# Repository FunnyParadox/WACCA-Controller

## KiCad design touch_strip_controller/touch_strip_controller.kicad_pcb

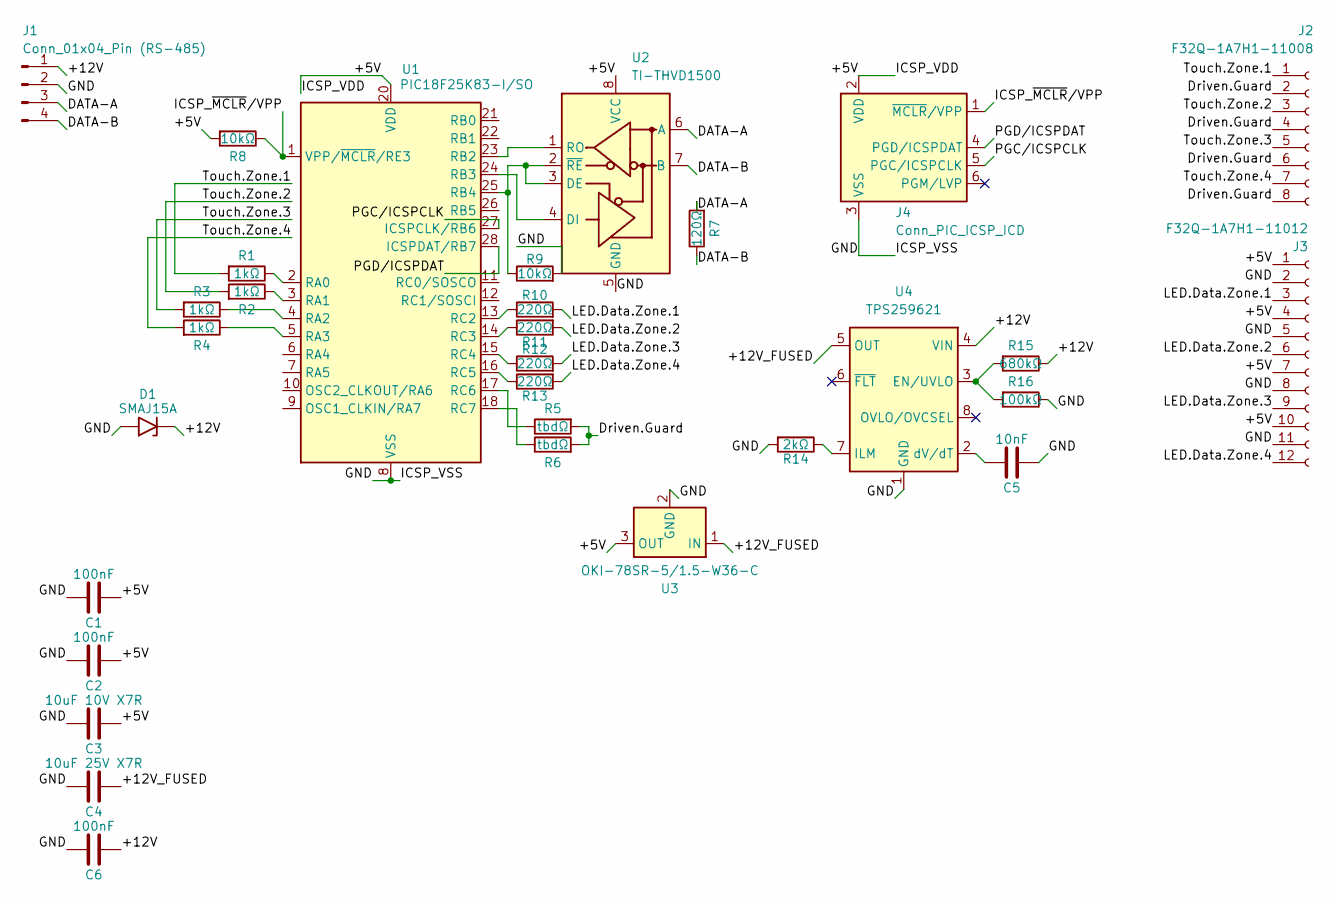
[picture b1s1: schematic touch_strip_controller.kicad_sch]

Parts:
C1, C2, C6: 100nF; C_0603_1608Metric
C3: 10uF 10V X7R; C_1206_3216Metric
C4: 10uF 25V X7R; C_1206_3216Metric
C5: 10nF; C_0603_1608Metric
D1: SMAJ15A; D_SMA
J1: Conn_01x04_Pin (RS-485); Amphenol_F32Q-1A7x1-11004_1x04-1MP_P0.5mm_Horizontal
J2: F32Q-1A7H1-11008; Amphenol_F32Q-1A7x1-11008_1x08-1MP_P0.5mm_Horizontal
J3: F32Q-1A7H1-11012; Amphenol_F32Q-1A7x1-11012_1x12-1MP_P0.5mm_Horizontal
J4: Conn_PIC_ICSP_ICD; PinHeader_1x06_P2.54mm_Vertical
R1, R2, R3, R4: 1kΩ; R_0603_1608Metric
R5, R6: tbdΩ; R_0603_1608Metric
R7: 120Ω; R_0603_1608Metric
R8, R9: 10kΩ; R_0603_1608Metric
R10, R11, R12, R13: 220Ω; R_0603_1608Metric
R14: 2kΩ; R_0603_1608Metric
R15: 680kΩ; R_0603_1608Metric
R16: 100kΩ; R_0603_1608Metric
U1: PIC18F25K83-I/SO; SOIC-28W_7.5x17.9mm_P1.27mm
U2: TI-THVD1500; SOIC-8_3.9x4.9mm_P1.27mm
U3: OKI-78SR-5/1.5-W36-C; Converter_DCDC_Murata_OKI-78SR_Vertical
U4: TPS259621; TI_SO-PowerPAD-8_ThermalVias

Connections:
/+5V: C1.1, C2.1, C3.1, J3.1, J3.4, J3.7, J3.10, J4.2 (VDD), R8.2, U1.20 (VDD), U2.8 (VCC), U3.3 (OUT)
/+12V: C6.2, D1.1 (A1), J1.1, R15.1, U4.4 (VIN)
/+12V_FUSED: C4.1, U3.1 (IN), U4.5 (OUT)
/DATA-A: J1.3, R7.2, U2.6 (A)
/DATA-B: J1.4, R7.1, U2.7 (B)
/Driven.Guard: J2.2, J2.4, J2.6, J2.8, R5.2, R6.2
/GND: C1.2, C2.2, C3.2, C4.2, C5.2, C6.1, D1.2 (A2), J1.2, J3.2, J3.5, J3.8, J3.11, J4.3 (VSS), R9.2, R14.2, R16.1, U1.8 (VSS), U1.19 (VSS), U2.5 (GND), U3.2 (GND), U4.1 (GND), U4.9 (GND)
/ICSP_~MCLR/VPP: J4.1 (~MCLR/VPP), R8.1, U1.1 (VPP/~MCLR/RE3)
/LED.Data.Zone.1: J3.3, R10.2
/LED.Data.Zone.2: J3.6, R11.2
/LED.Data.Zone.3: J3.9, R12.2
/LED.Data.Zone.4: J3.12, R13.2
/PGC/ICSPCLK: J4.5 (PGC/ICSPCLK), U1.27 (ICSPCLK/RB6)
/PGD/ICSPDAT: J4.4 (PGD/ICSPDAT), U1.28 (ICSPDAT/RB7)
/Touch.Zone.1: J2.1, R1.2
/Touch.Zone.2: J2.3, R2.2
/Touch.Zone.3: J2.5, R3.2
/Touch.Zone.4: J2.7, R4.2
unnamed: R1.1, U1.2 (RA0)
unnamed: R2.1, U1.3 (RA1)
unnamed: R3.1, U1.4 (RA2)
unnamed: R4.1, U1.5 (RA3)
unnamed: U1.23 (RB2), U2.1 (RO)
unnamed: U1.24 (RB3), U2.4 (DI)
unnamed: R9.1, U1.25 (RB4), U2.2 (~RE), U2.3 (DE)
unnamed: R10.1, U1.13 (RC2)
unnamed: R11.1, U1.14 (RC3)
unnamed: R12.1, U1.15 (RC4)
unnamed: R13.1, U1.16 (RC5)
unnamed: R5.1, U1.17 (RC6)
unnamed: R6.1, U1.18 (RC7)
unnamed: R15.2, R16.2, U4.3 (EN/UVLO)
unnamed: R14.1, U4.7 (ILM)
unnamed: C5.1, U4.2 (dV/dT)

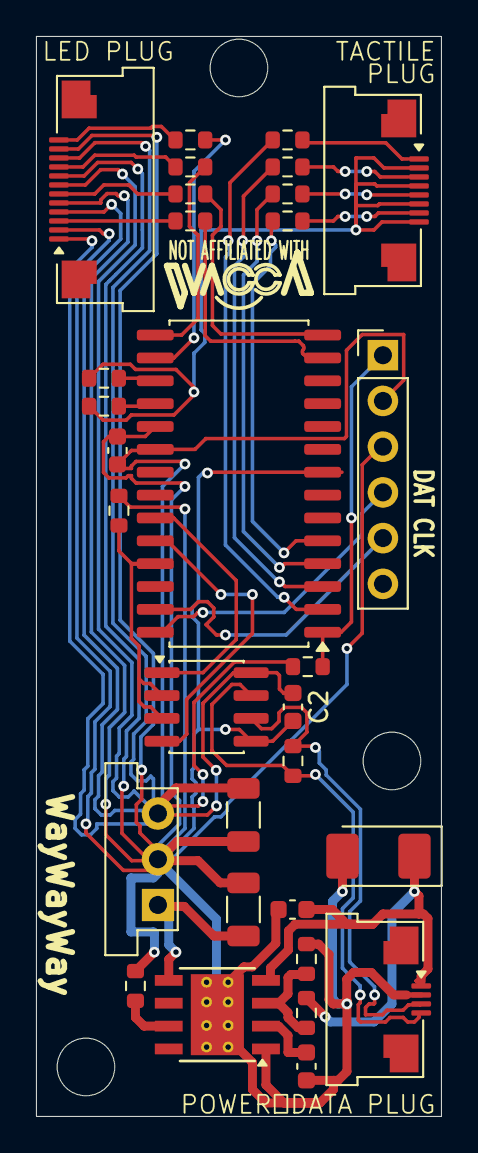
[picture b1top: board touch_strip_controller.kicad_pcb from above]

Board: 2 copper layers, 22.5 x 60.0 mm, 31 parts (0 on the bottom side), 34 nets.
